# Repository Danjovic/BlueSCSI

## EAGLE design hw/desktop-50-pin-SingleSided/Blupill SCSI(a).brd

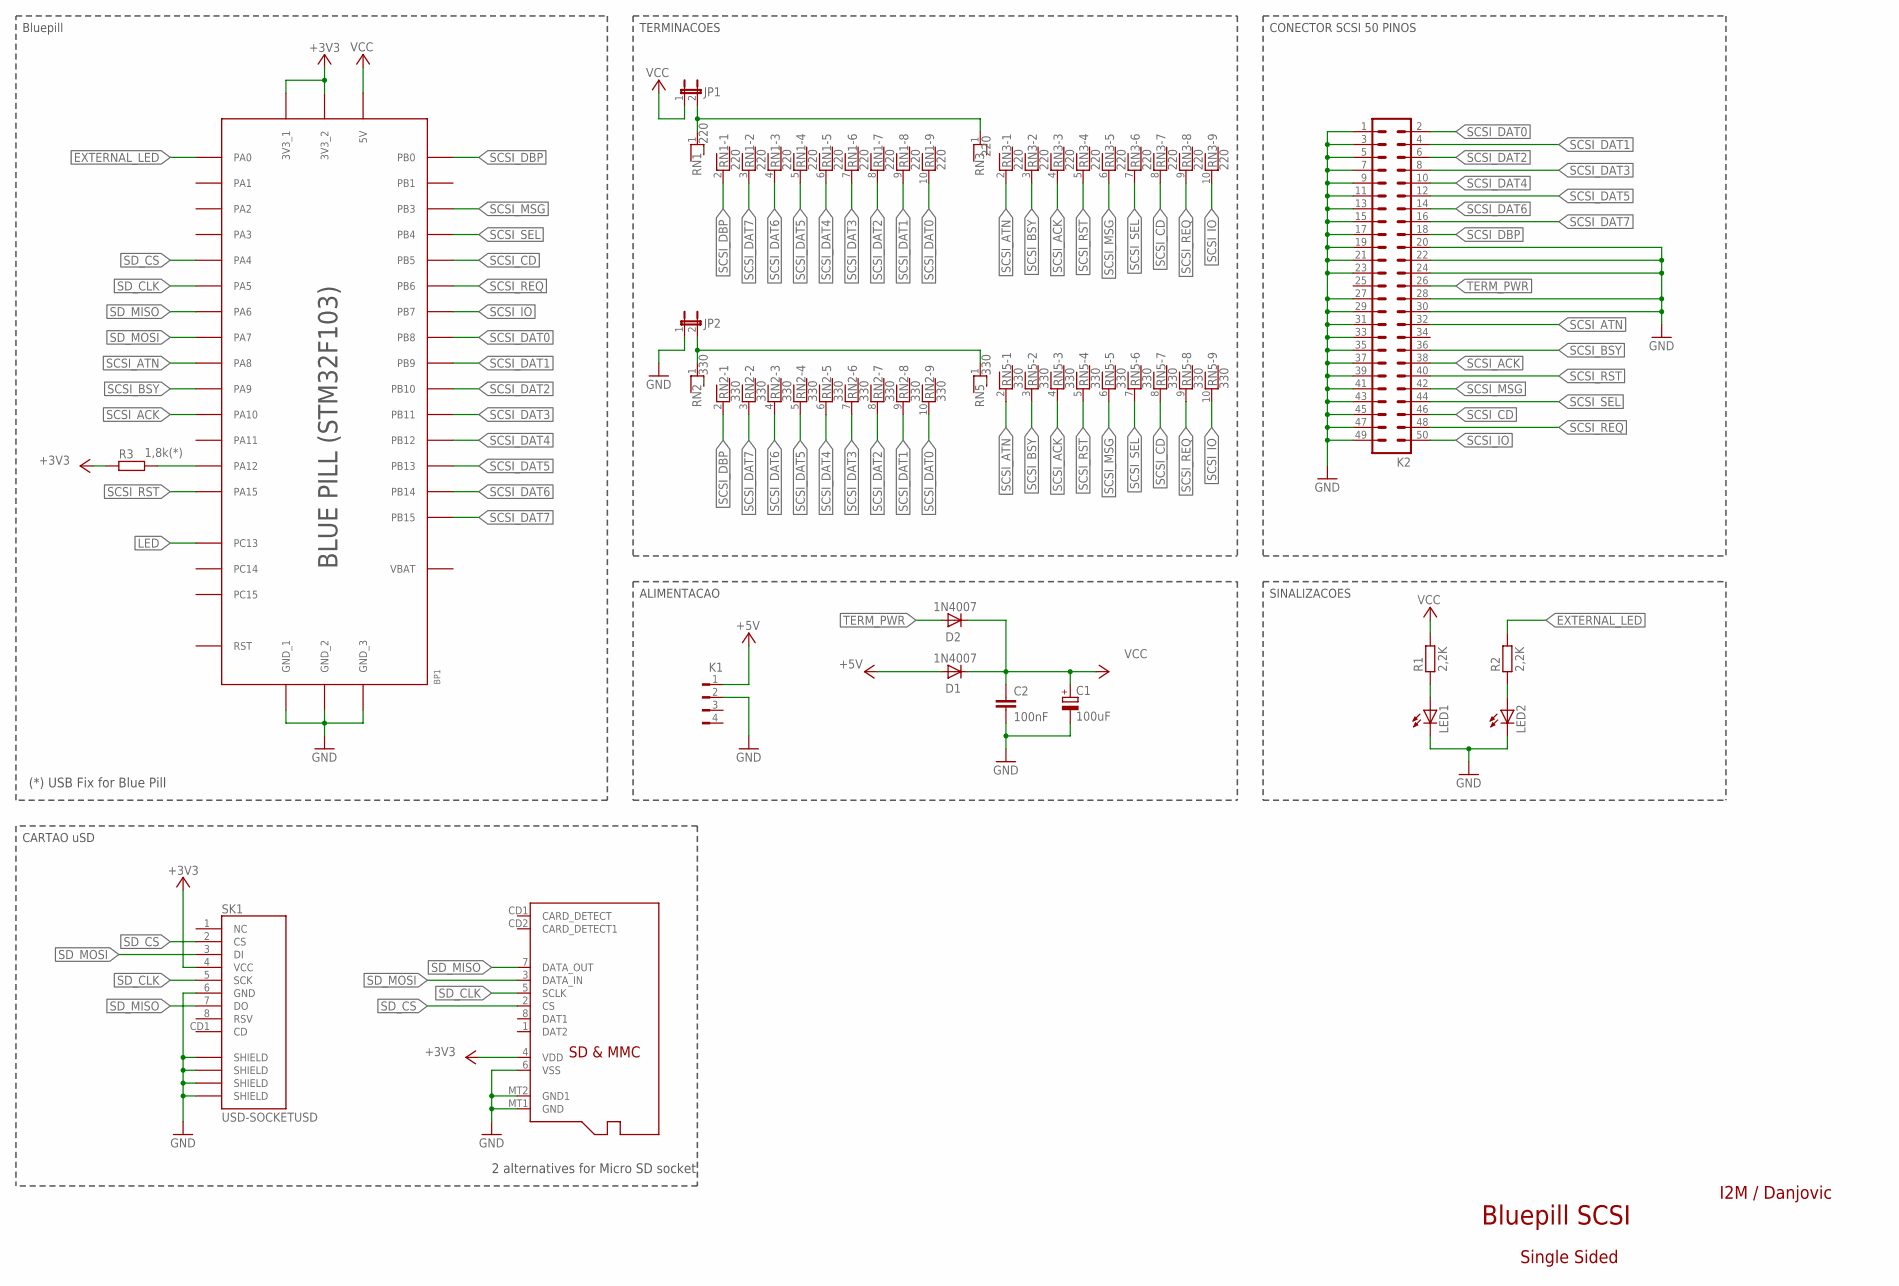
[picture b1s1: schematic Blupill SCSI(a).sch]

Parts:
BP1: BLUE_PILL
C1: 100uF; E2,5-7
C2: 100nF; C050-025X075
D1, D2: 1N4007; DO41-10
JP1, JP2: JP1E; JP1
K1: FLOP-4W; FLOP-4V
K2: ML50L
LED1, LED2: LED3MM
R1, R2: 2,2K; 0207/10
R3: 1,8k(*); 0207/10
RN1, RN3: 220; RN-10
RN2, RN5: 330; RN-10
SK1: USD-SOCKETUSD; USD-SOCKET-PP
U$2: MICROSD

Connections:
+3V3: BP1.3,3V_1 (3V3_1), BP1.3,3V_2 (3V3_2), R3.1, SK1.4 (VCC), U$2.4 (VDD)
+5V: D1.A, K1.1
EXTERNAL_LED: BP1.A0, R2.2
GND: BP1.GND1 (GND_1), BP1.GND2 (GND_2), BP1.GND3 (GND_3), C1.-, C2.2, JP2.1, K1.2, K2.1, K2.3, K2.5, K2.7, K2.9, K2.11, K2.13, K2.15, K2.17, K2.19, K2.20, K2.21, K2.22, K2.23, K2.24, K2.27, K2.28, K2.29, K2.30, K2.31, K2.33, K2.35, K2.37, K2.39, K2.41, K2.43, K2.45, K2.47, K2.49, LED1.K (C), LED2.K (C), SK1.6 (GND), SK1.GND1 (SHIELD), SK1.GND2 (SHIELD), SK1.GND3 (SHIELD), SK1.GND4 (SHIELD), U$2.6 (VSS), U$2.MT1 (GND), U$2.MT2 (GND1)
LED: BP1.C13
unnamed: JP2.2, RN2.1, RN5.1
unnamed: LED1.A, R1.1
unnamed: LED2.A, R2.1
unnamed: JP1.2, RN1.1, RN3.1
unnamed: BP1.A12, R3.2
SCSI_ACK: BP1.A10, K2.38, RN3.4, RN5.4
SCSI_ATN: BP1.A8, K2.32, RN3.2, RN5.2
SCSI_BSY: BP1.A9, K2.36, RN3.3, RN5.3
SCSI_CD: BP1.B5, K2.46, RN3.8, RN5.8
SCSI_DAT0: BP1.B8, K2.2, RN1.10, RN2.10
SCSI_DAT1: BP1.B9, K2.4, RN1.9, RN2.9
SCSI_DAT2: BP1.B10, K2.6, RN1.8, RN2.8
SCSI_DAT3: BP1.B11, K2.8, RN1.7, RN2.7
SCSI_DAT4: BP1.B12, K2.10, RN1.6, RN2.6
SCSI_DAT5: BP1.B13, K2.12, RN1.5, RN2.5
SCSI_DAT6: BP1.B14, K2.14, RN1.4, RN2.4
SCSI_DAT7: BP1.B15, K2.16, RN1.3, RN2.3
SCSI_DBP: BP1.B0, K2.18, RN1.2, RN2.2
SCSI_IO: BP1.B7, K2.50, RN3.10, RN5.10
SCSI_MSG: BP1.B3, K2.42, RN3.6, RN5.6
SCSI_REQ: BP1.B6, K2.48, RN3.9, RN5.9
SCSI_RST: BP1.A15, K2.40, RN3.5, RN5.5
SCSI_SEL: BP1.B4, K2.44, RN3.7, RN5.7
SD_CLK: BP1.A5, SK1.5 (SCK), U$2.5 (SCLK)
SD_CS: BP1.A4, SK1.2 (CS), U$2.2 (CS)
SD_MISO: BP1.A6, SK1.7 (DO), U$2.7 (DATA_OUT)
SD_MOSI: BP1.A7, SK1.3 (DI), U$2.3 (DATA_IN)
TERM_PWR: D2.A, K2.26
VBAT: BP1.VB (VBAT)
VCC: BP1.5V, C1.+, C2.1, D1.C, D2.C, JP1.1, R1.2

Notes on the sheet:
Bluepill SCSI
Bluepill
CONECTOR SCSI 50 PINOS
TERMINACOES
ALIMENTACAO
SINALIZACOES
CARTAO uSD
Single Sided
2 alternatives for Micro SD socket
(*) USB Fix for Blue Pill
I2M / Danjovic

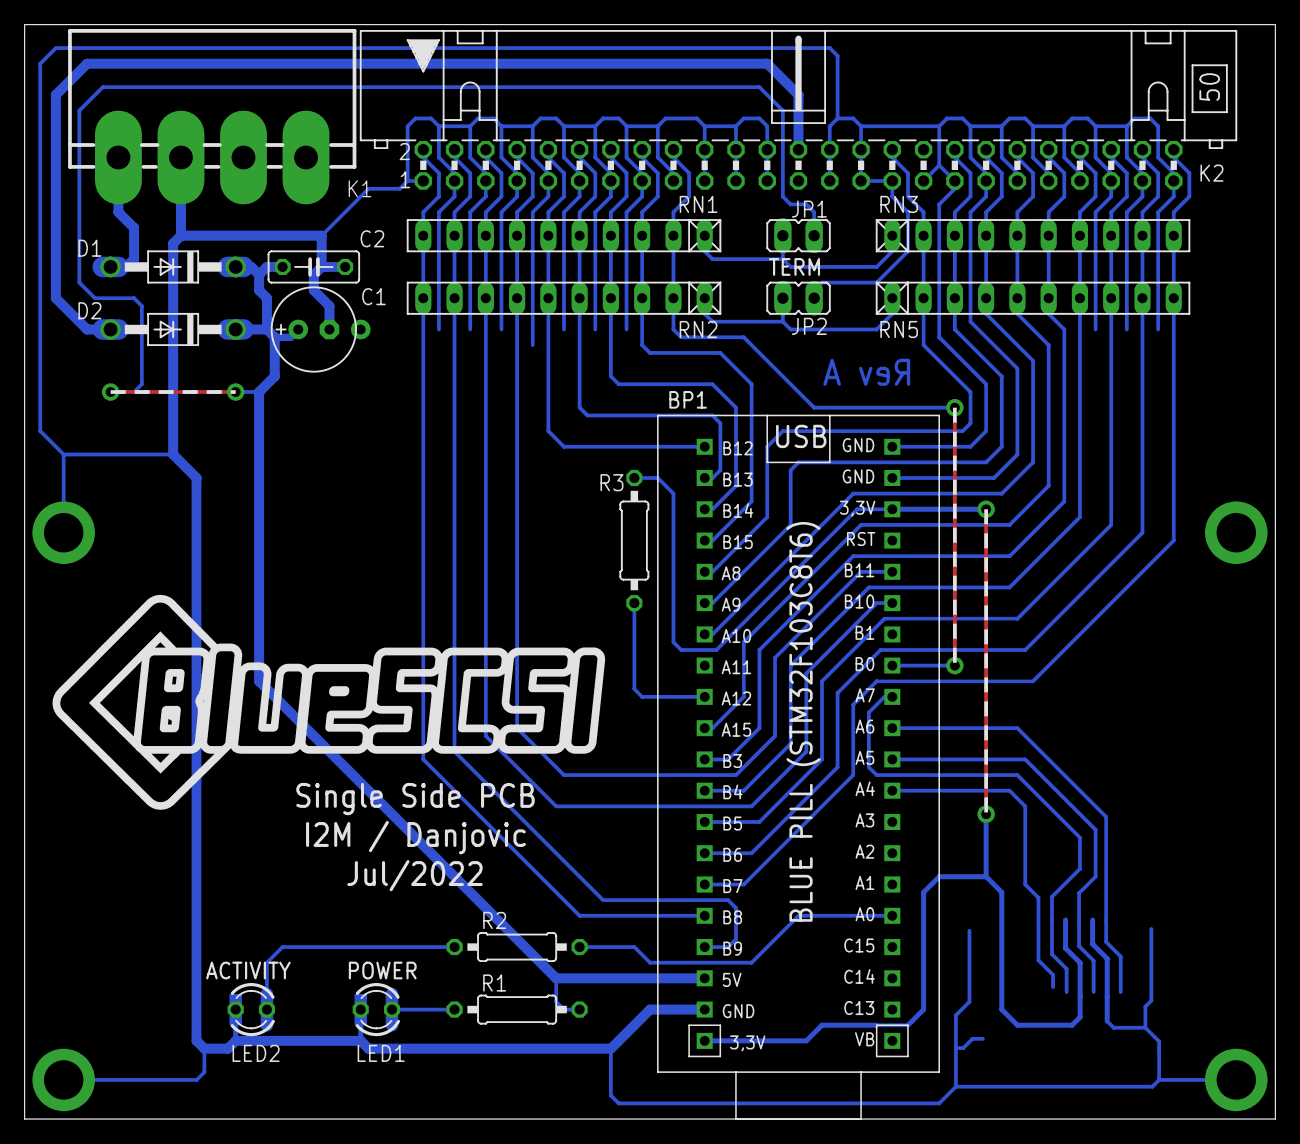
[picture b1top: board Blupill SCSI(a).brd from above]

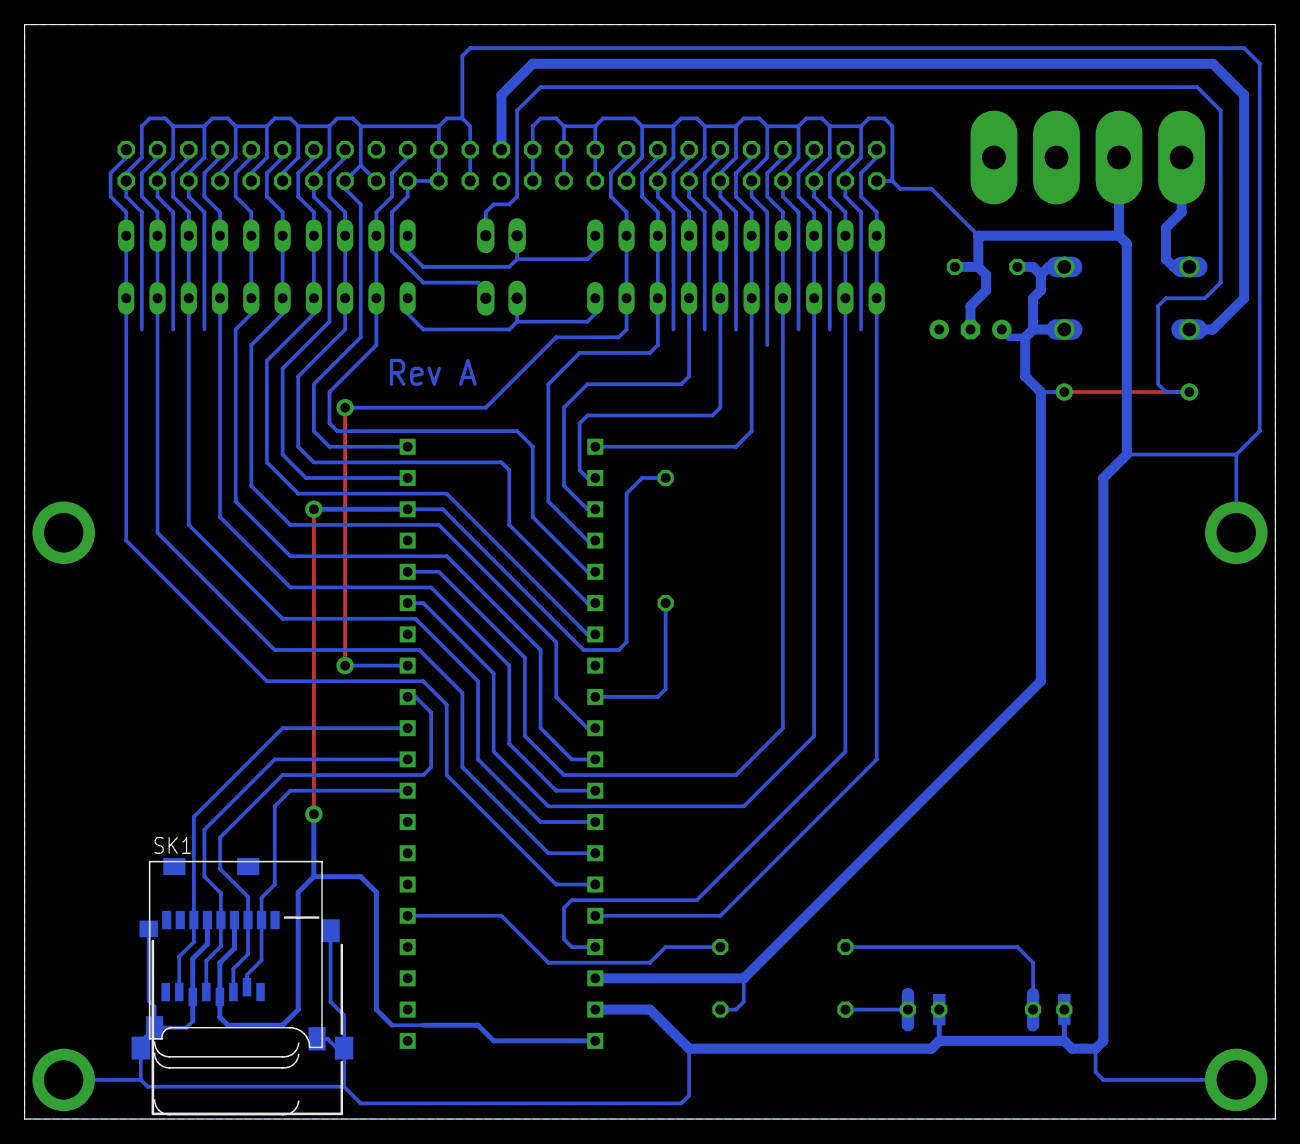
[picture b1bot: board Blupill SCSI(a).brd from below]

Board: 2 copper layers, 101.6 x 88.9 mm, 20 parts (2 on the bottom side), 33 nets.

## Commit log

2022-07-08 single sided PCB, 4 inch hdd form factor
2022-07-17 Revision H. Redrawn in Eagle 5.8
